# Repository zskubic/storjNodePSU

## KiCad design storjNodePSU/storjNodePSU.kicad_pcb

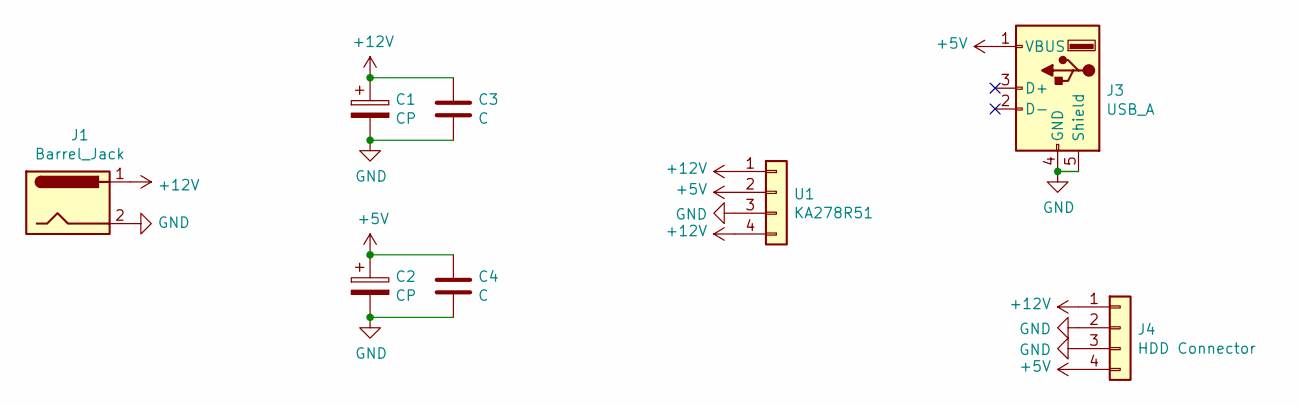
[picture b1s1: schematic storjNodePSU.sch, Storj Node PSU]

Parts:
C1, C2: CP; CP_Radial_D5.0mm_P2.50mm
C3, C4: C; C_Disc_D3.0mm_W2.0mm_P2.50mm
J1: Barrel_Jack; BarrelJack_Horizontal
J3: USB_A; USB_A_CONNFLY_DS1095-WNR0
J4: HDD Connector; PinHeader_1x04_P2.54mm_Vertical
U1: KA278R51; TO-220F-4_Vertical

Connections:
+5V: C2.1, C4.1, J3.1 (VBUS), J4.4, U1.2
+12V: C1.1, C3.1, J1.1, J4.1, U1.1, U1.4
GND: C1.2, C2.2, C3.2, C4.2, J1.2, J3.4 (GND), J3.5 (Shield), J4.2, J4.3, U1.3

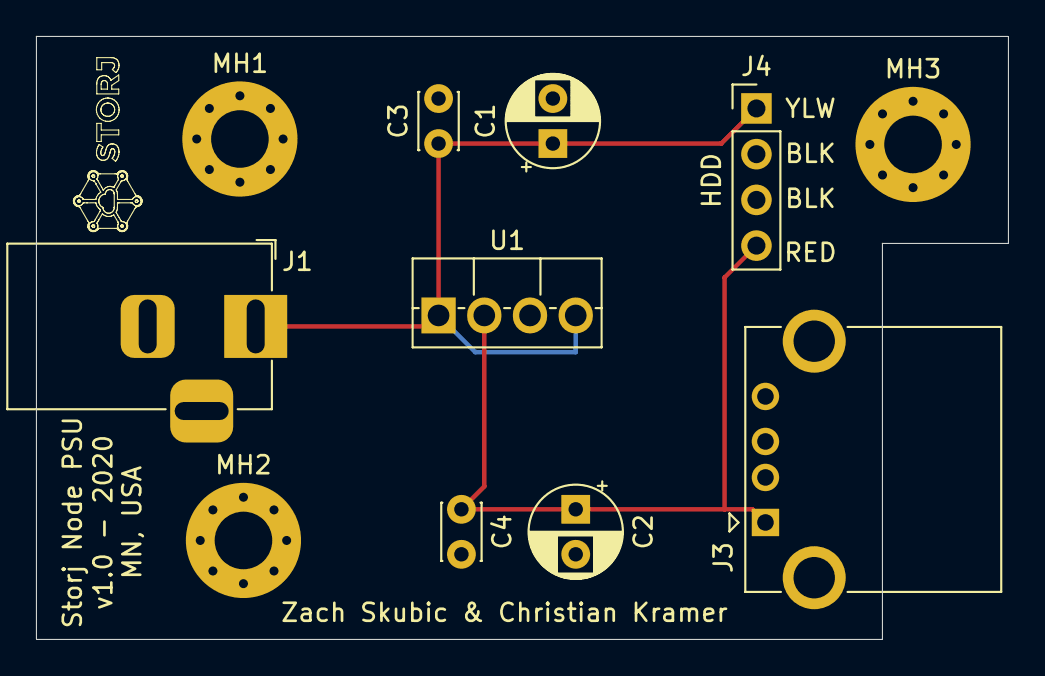
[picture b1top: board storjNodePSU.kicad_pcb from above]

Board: 2 copper layers, 54.0 x 33.5 mm, 11 parts (0 on the bottom side), 3 nets.

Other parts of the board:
MH1, MH2, MH3: MountingHole_3.2mm_M3_Pad_Via

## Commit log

2020-05-29 Completed version 1.
2020-05-30 found datasheet for voltage regulator
2020-05-30 added 3D models to PCB
2020-05-30 removed pin header from 3d view
2020-05-30 rendered image
